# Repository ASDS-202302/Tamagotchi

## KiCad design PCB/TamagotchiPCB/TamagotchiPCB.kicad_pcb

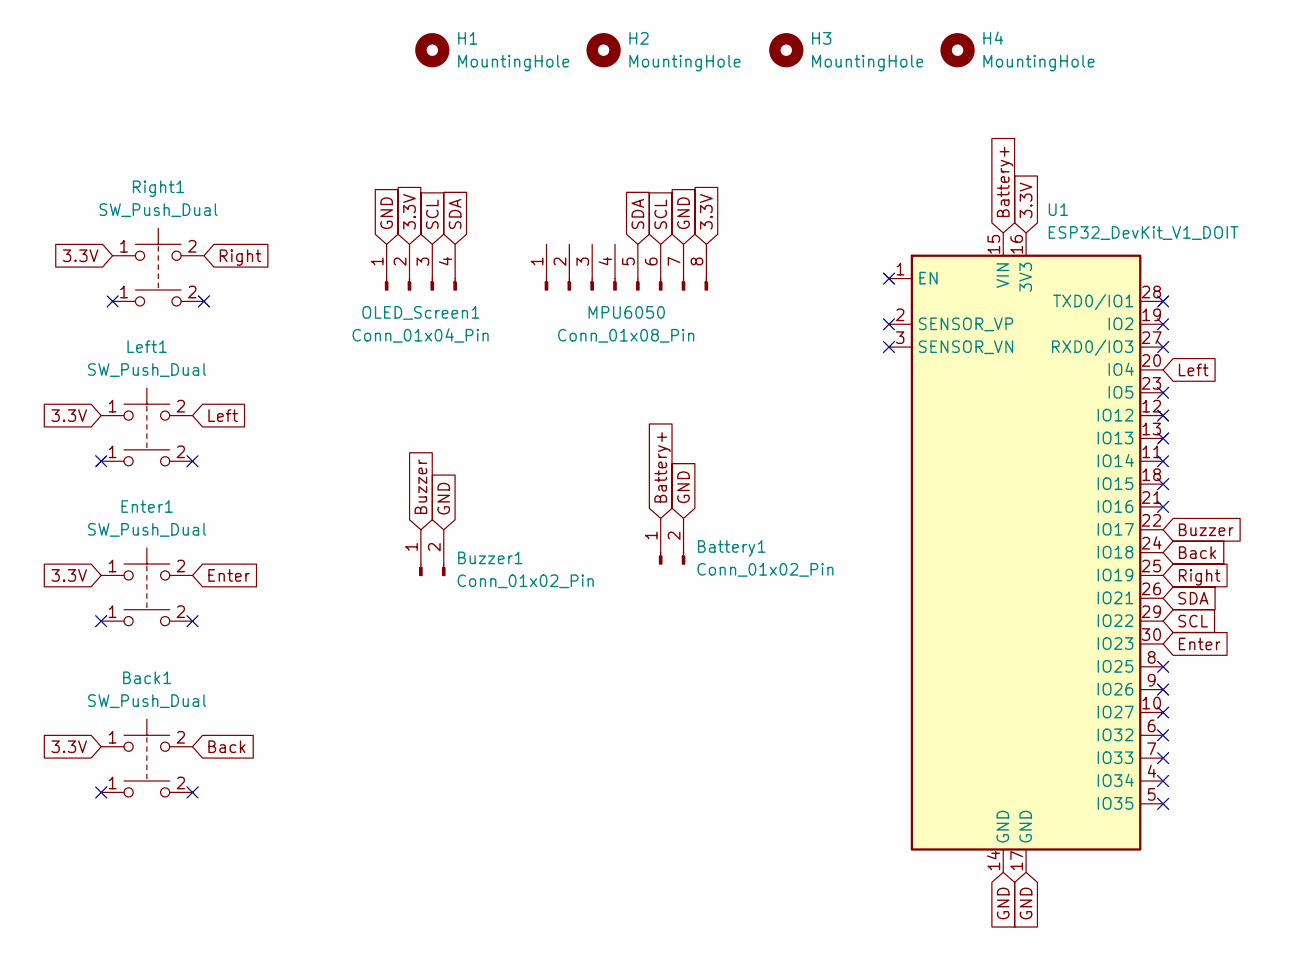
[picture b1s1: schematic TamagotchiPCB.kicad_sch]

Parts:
Back1: SW_Push_Dual; SW_PUSH-12mm
Battery1: Conn_01x02_Pin; PinHeader_1x02_P2.54mm_Vertical
Buzzer1: Conn_01x02_Pin; PinHeader_1x02_P2.54mm_Vertical
Enter1: SW_Push_Dual; SW_PUSH-12mm
H1, H2, H3, H4: MountingHole; MountingHole_3mm
Left1: SW_Push_Dual; SW_PUSH-12mm
MPU6050: Conn_01x08_Pin; PinHeader_1x08_P2.54mm_Vertical
OLED_Screen1: Conn_01x04_Pin; PinHeader_1x04_P2.54mm_Vertical
Right1: SW_Push_Dual; SW_PUSH-12mm
U1: ESP32_DevKit_V1_DOIT; esp32_devkit_v1_doit

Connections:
3.3V: Back1.1, Enter1.1, Left1.1, MPU6050.8, OLED_Screen1.2, Right1.1, U1.16 (3V3)
Back: Back1.2, U1.24 (IO18)
Battery+: Battery1.1, U1.15 (VIN)
Buzzer: Buzzer1.1, U1.22 (IO17)
Enter: Enter1.2, U1.30 (IO23)
GND: Battery1.2, Buzzer1.2, MPU6050.7, OLED_Screen1.1, U1.14 (GND), U1.17 (GND)
Left: Left1.2, U1.20 (IO4)
Right: Right1.2, U1.25 (IO19)
SCL: MPU6050.6, OLED_Screen1.3, U1.29 (IO22)
SDA: MPU6050.5, OLED_Screen1.4, U1.26 (IO21)

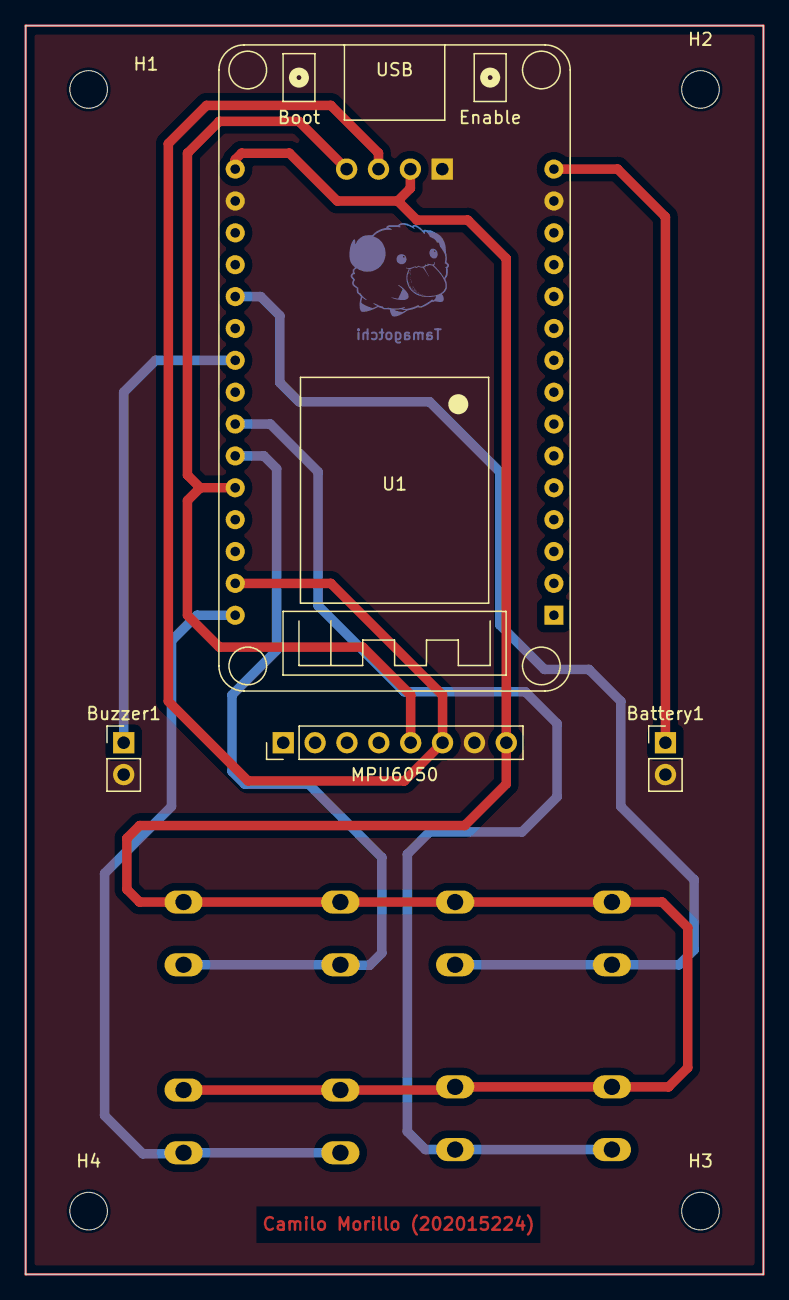
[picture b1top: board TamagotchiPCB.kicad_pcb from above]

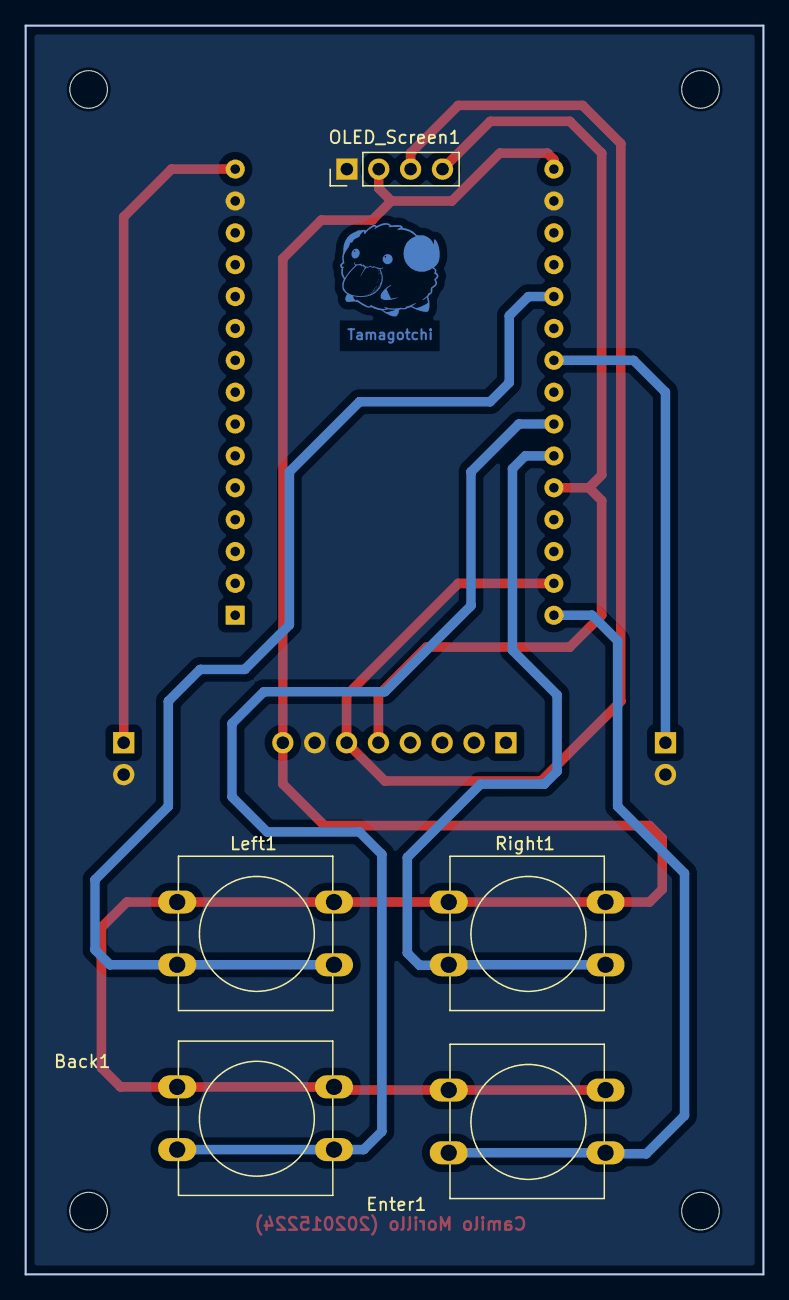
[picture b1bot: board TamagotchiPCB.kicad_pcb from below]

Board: 2 copper layers, 58.8 x 99.5 mm, 13 parts (5 on the bottom side), 10 nets.

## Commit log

2023-11-08 change name
2023-11-15 FreeRTOS template main
2023-11-15 Update comments
2023-11-19 edit pcb imagenes
2023-11-22 update main
2023-11-22 add image
2023-11-24 update status
2023-11-29 final commit
2023-11-29 final
